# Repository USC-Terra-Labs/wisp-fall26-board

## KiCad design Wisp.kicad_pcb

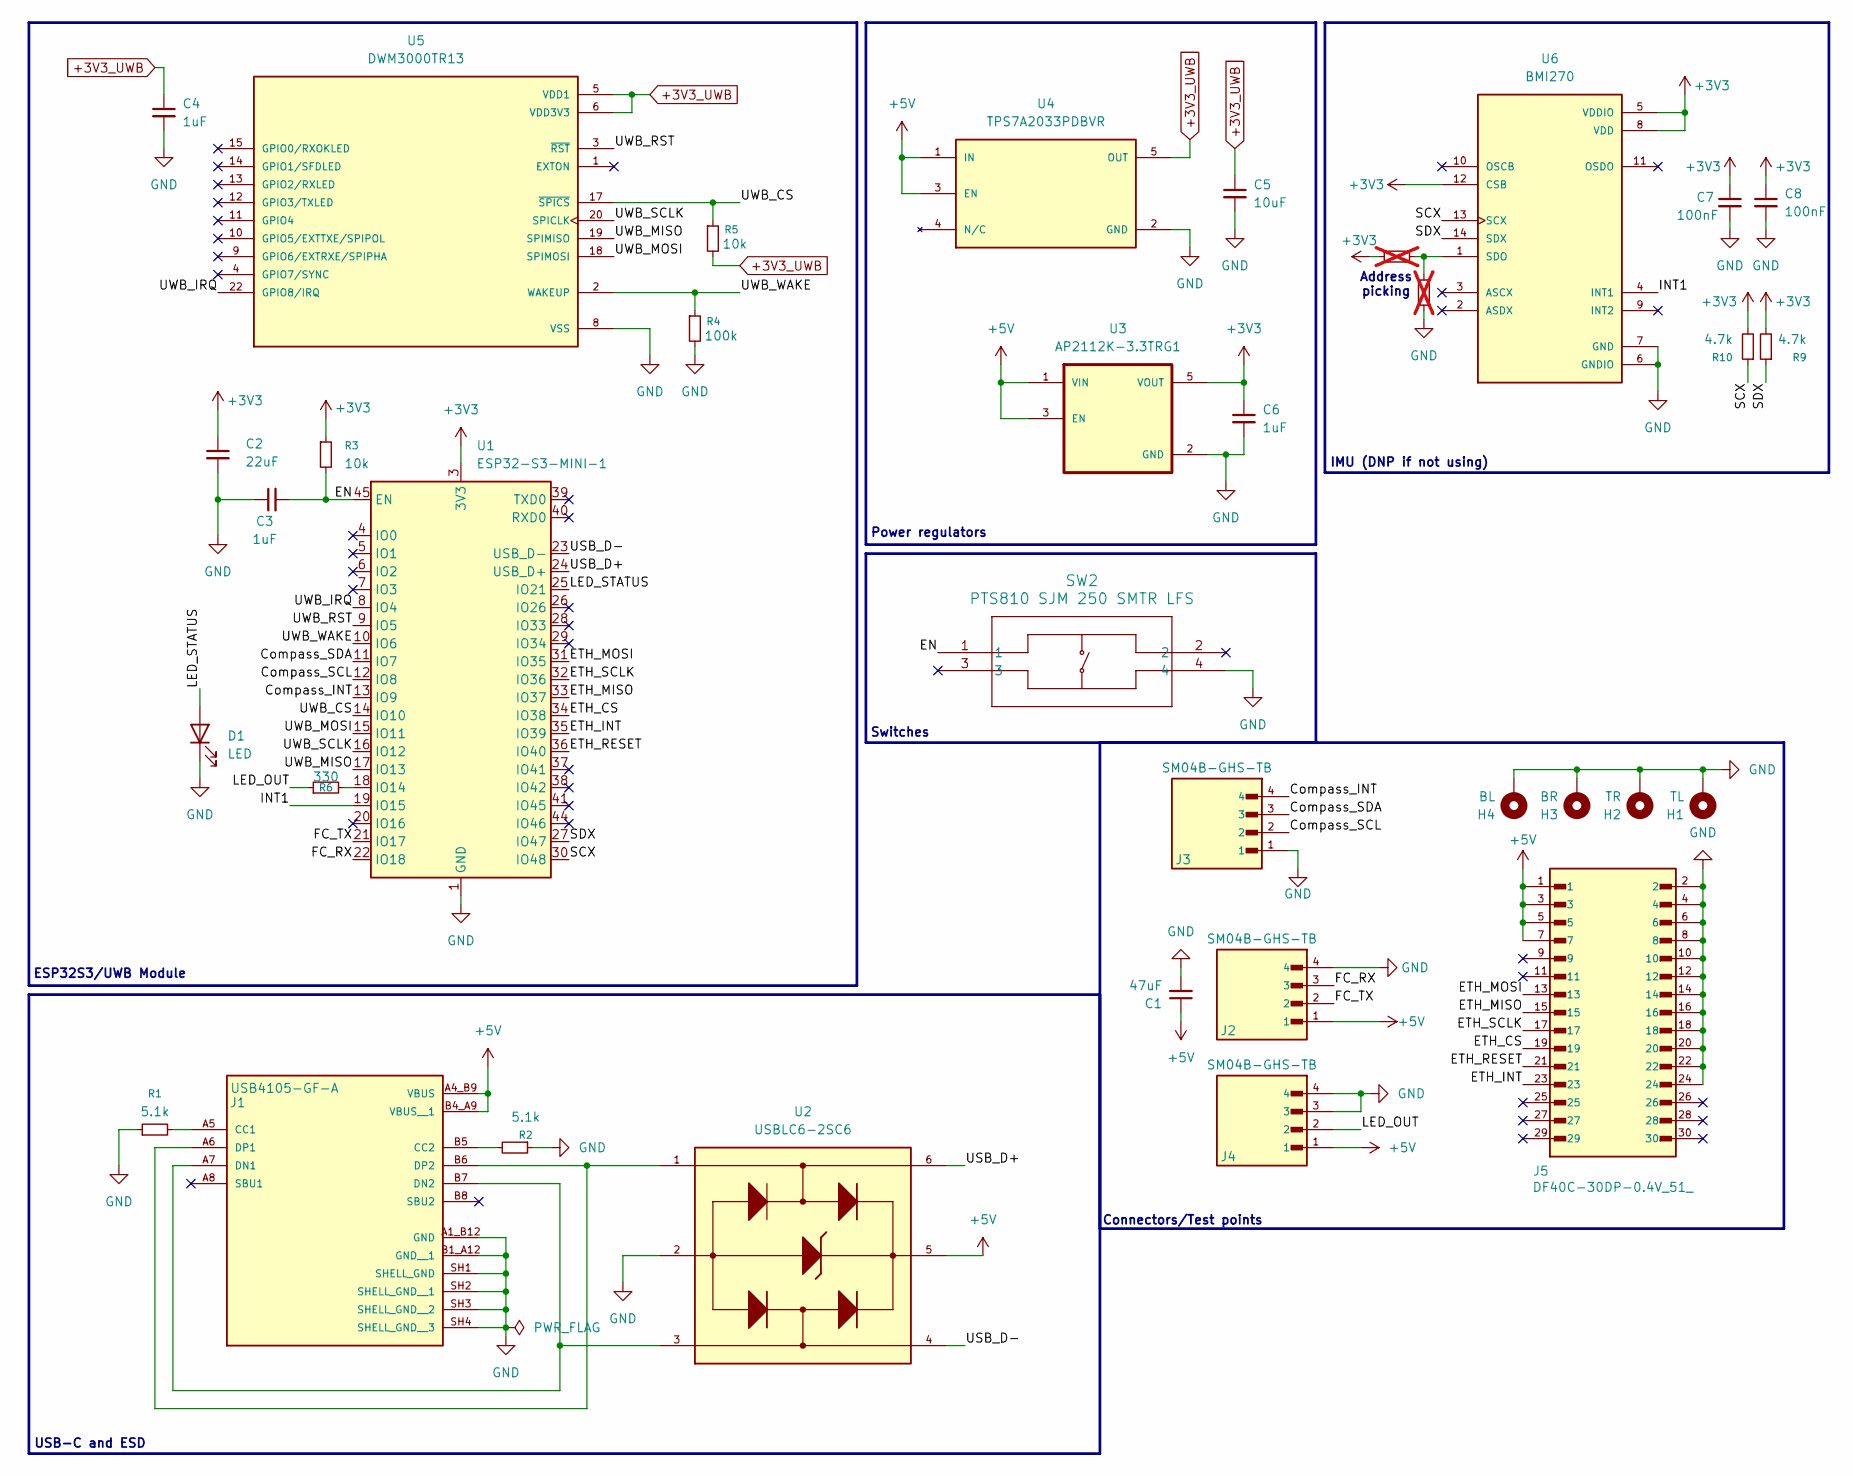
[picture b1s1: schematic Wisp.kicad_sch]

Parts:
C1: 47uF; C_0603_1608Metric
C2: 22uF; C_0603_1608Metric
C3, C4, C6: 1uF; C_0603_1608Metric
C5: 10uF; C_0603_1608Metric
C7, C8: 100nF; C_0603_1608Metric
D1: LED; LED_0603_1608Metric
H1: TL; MountingHole_3.2mm_M3_Pad_Via
H2: TR; MountingHole_3.2mm_M3_Pad_Via
H3: BR; MountingHole_3.2mm_M3_Pad_Via
H4: BL; MountingHole_3.2mm_M3_Pad_Via
J1: USB4105-GF-A; GCT_USB4105-GF-A; PARTREV B4
J2, J3, J4: SM04B-GHS-TB; JST_SM04B-GHS-TB
J5: DF40C-30DP-0.4V_51_; HIROSE_DF40C-30DP-0.4V_51_; MPN DF40C-30DP-0.4V(51)
R1, R2: 5.1k; R_0603_1608Metric
R3, R5: 10k; R_0603_1608Metric
R4: 100k; R_0603_1608Metric
R6: 330; R_0603_1608Metric
R7, R8: R_Small; R_0402_1005Metric; not fitted
R9, R10: 4.7k; R_0603_1608Metric
SW2: PTS810 SJM 250 SMTR LFS; PTS810_CNK
U1: ESP32-S3-MINI-1; ESP32-S2-MINI-1
U2: USBLC6-2SC6; SOT95P280X145-6N
U3: AP2112K-3.3TRG1; SOT95P285X140-5N; PARTREV 2-2; DigiKey_Part_Number AP2112K-3.3TRG1DICT-ND
U4: TPS7A2033PDBVR; SOT95P280X145-5N; PARTREV H
U5: DWM3000TR13; XCVR_DWM3000TR13; PARTREV B
U6: BMI270; XDCR_BMI270; MPN BMI270

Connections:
+3V3: C2.1, C6.1, C7.1, C8.1, R3.1, R7.1, R9.2, R10.2, U1.3 (3V3), U3.5 (VOUT), U6.5 (VDDIO), U6.8 (VDD), U6.12 (CSB)
+3V3_UWB: C4.1, C5.1, R5.2, U4.5 (OUT), U5.5 (VDD1), U5.6 (VDD3V3), U5.7 (VDD3V3)
+5V: C1.1, J1.A4_B9 (VBUS), J1.B4_A9 (VBUS__1), J2.1, J4.1, J5.1, J5.3, J5.5, J5.7, U2.5, U3.1 (VIN), U3.3 (EN), U4.1 (IN), U4.3 (EN)
/Compass_INT: J3.4, U1.13 (IO9)
/Compass_SCL: J3.2, U1.12 (IO8)
/Compass_SDA: J3.3, U1.11 (IO7)
/EN: C3.2, R3.2, SW2.1, U1.45 (EN)
/ETH_CS: J5.19, U1.34 (IO38)
/ETH_INT: J5.23, U1.35 (IO39)
/ETH_MISO: J5.15, U1.33 (IO37)
/ETH_MOSI: J5.13, U1.31 (IO35)
/ETH_RESET: J5.21, U1.36 (IO40)
/ETH_SCLK: J5.17, U1.32 (IO36)
/FC_RX: J2.3, U1.22 (IO18)
/FC_TX: J2.2, U1.21 (IO17)
/INT1: U1.19 (IO15), U6.4 (INT1)
/LED_OUT: J4.2, R6.1
/LED_STATUS: D1.2 (A), U1.25 (IO21)
/SCX: R10.1, U1.30 (IO48), U6.13 (SCX)
/SDX: R9.1, U1.27 (IO47), U6.14 (SDX)
/USB_D+: U1.24 (USB_D+), U2.6
/USB_D-: U1.23 (USB_D-), U2.4
/UWB_CS: R5.1, U1.14 (IO10), U5.17 (~SPICS)
/UWB_IRQ: U1.8 (IO4), U5.22 (GPIO8/IRQ)
/UWB_MISO: U1.17 (IO13), U5.19 (SPIMISO)
/UWB_MOSI: U1.15 (IO11), U5.18 (SPIMOSI)
/UWB_RST: U1.9 (IO5), U5.3 (~RST)
/UWB_SCLK: U1.16 (IO12), U5.20 (SPICLK)
/UWB_WAKE: R4.1, U1.10 (IO6), U5.2 (WAKEUP)
GND: C1.2, C2.2, C3.1, C4.2, C5.2, C6.2, C7.2, C8.2, D1.1 (K), H1.MP, H2.MP, H3.MP, H4.MP, J1.A1_B12 (GND), J1.B1_A12 (GND__1), J1.SH1 (SHELL_GND), J1.SH2 (SHELL_GND__1), J1.SH3 (SHELL_GND__2), J1.SH4 (SHELL_GND__3), J2.4, J3.1, J4.3, J4.4, J5.2, J5.4, J5.6, J5.8, J5.10, J5.12, J5.14, J5.16, J5.18, J5.20, J5.22, J5.24, R1.1, R2.1, R4.2, R8.1, SW2.4, U1.1 (GND), U1.2 (GND), U1.42 (GND), U1.43 (GND), U1.46 (GND), U1.47 (GND), U1.48 (GND), U1.49 (GND), U1.50 (GND), U1.51 (GND), U1.52 (GND), U1.53 (GND), U1.54 (GND), U1.55 (GND), U1.56 (GND), U1.57 (GND), U1.58 (GND), U1.59 (GND), U1.60 (GND), U1.61 (GND), U1.62 (GND), U1.63 (GND), U1.64 (GND), U1.65 (GND), U2.2, U3.2 (GND), U4.2 (GND), U5.8 (VSS), U5.16 (VSS), U5.21 (VSS), U5.23 (VSS), U5.24 (VSS), U6.6 (GNDIO), U6.7 (GND)
unnamed: J1.A5 (CC1), R1.2
unnamed: J1.B5 (CC2), R2.2
unnamed: J1.A7 (DN1), J1.B7 (DN2), U2.3
unnamed: J1.A6 (DP1), J1.B6 (DP2), U2.1
unnamed: R6.2, U1.18 (IO14)
unnamed: R7.2, R8.2, U6.1 (SDO)

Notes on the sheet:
Address picking
Switches
USB-C and ESD
ESP32S3/UWB Module
IMU (DNP if not using)
Power regulators
Connectors/Test points

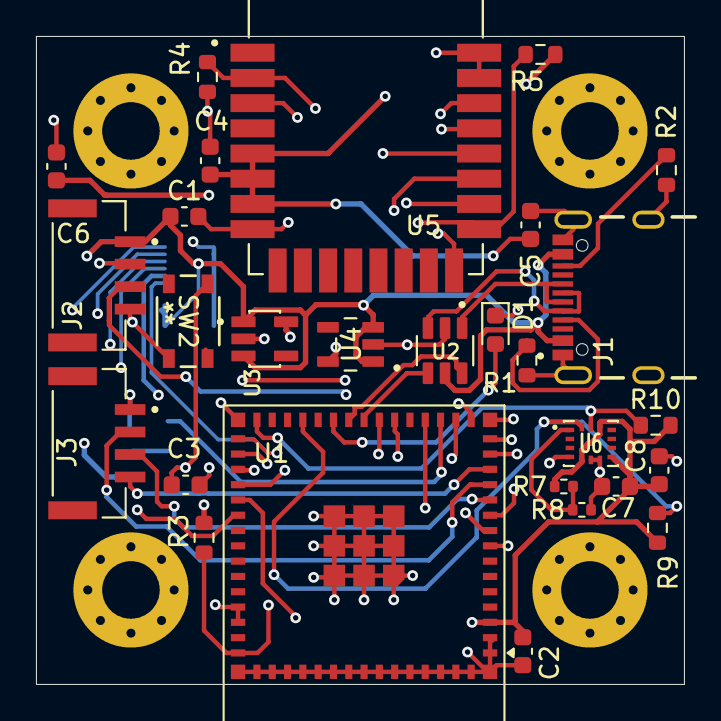
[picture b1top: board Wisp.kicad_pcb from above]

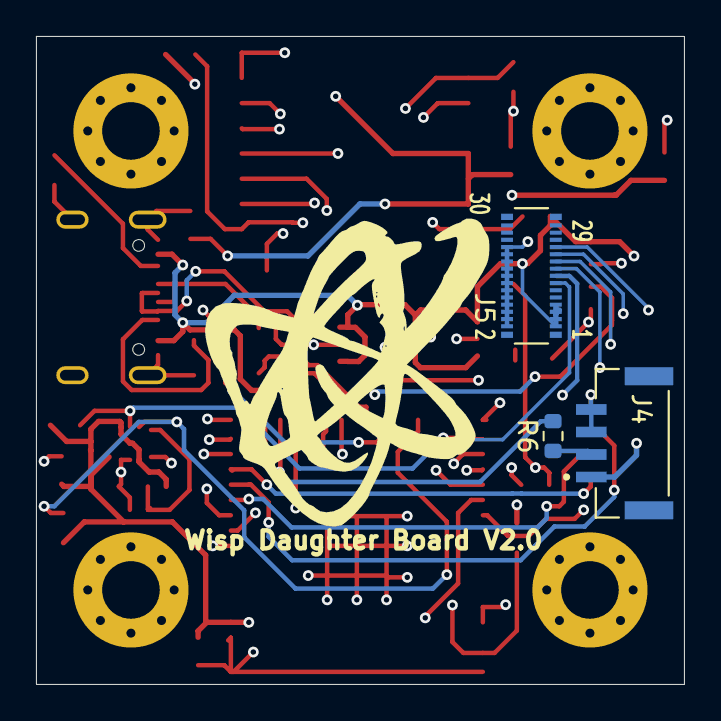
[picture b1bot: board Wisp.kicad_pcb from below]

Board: 4 copper layers, 36.0 x 36.0 mm, 35 parts (3 on the bottom side), 36 nets.

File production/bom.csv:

Designator,Footprint,Quantity,Value,LCSC Part #
C1,0603,1,47uF,
C2,0603,1,22uF,
"C3, C4, C6",0603,3,1uF,
C5,0603,1,10uF,
"C7, C8",0603,2,100nF,
D1,0603,1,LED,
J1,GCT_USB4105-GF-A,1,USB4105-GF-A,
"J2, J3, J4",JST_SM04B-GHS-TB,3,SM04B-GHS-TB,
J5,HIROSE_DF40C-30DP-0.4V_51_,1,DF40C-30DP-0.4V_51_,DF40C-30DP-0.4V(51)
"R1, R2",0603,2,5.1k,
"R10, R9",0603,2,4.7k,
"R3, R5",0603,2,10k,
R4,0603,1,100k,
R6,0603,1,330,
"R7, R8",0402,2,R_Small,
SW2,PTS810_CNK,1,PTS810 SJM 250 SMTR LFS,
U1,ESP32-S2-MINI-1,1,ESP32-S3-MINI-1,
U2,SOT95P280X145-6N,1,USBLC6-2SC6,
U3,SOT95P285X140-5N,1,AP2112K-3.3TRG1,
U4,SOT95P280X145-5N,1,TPS7A2033PDBVR,
U5,XCVR_DWM3000TR13,1,DWM3000TR13,
U6,XDCR_BMI270,1,BMI270,BMI270
